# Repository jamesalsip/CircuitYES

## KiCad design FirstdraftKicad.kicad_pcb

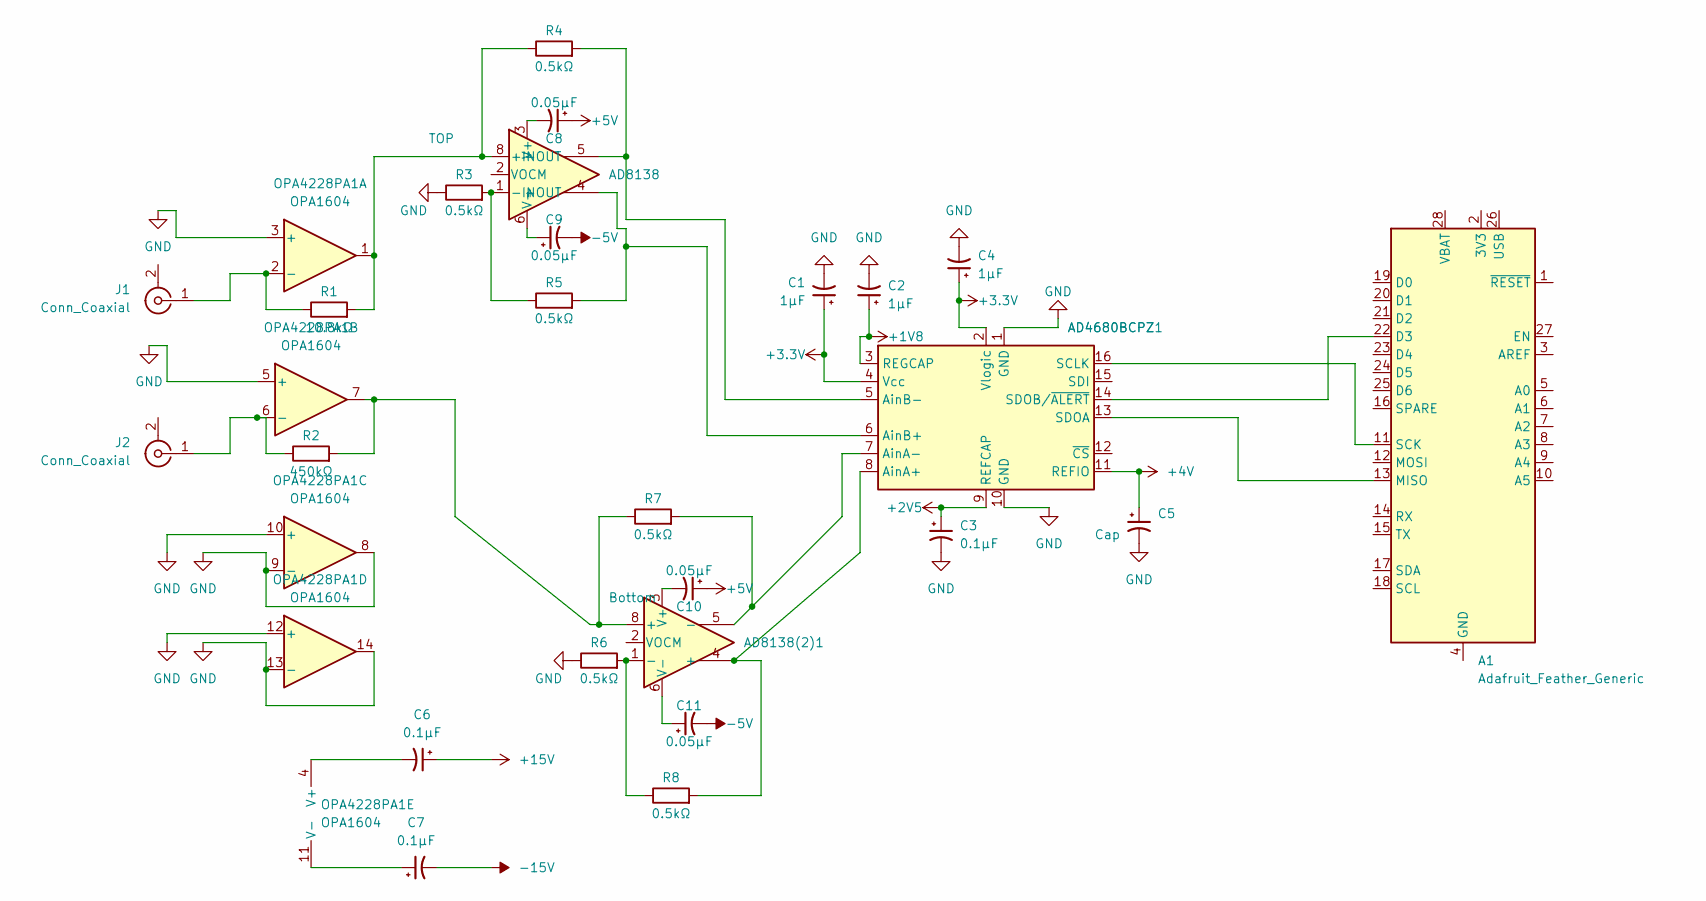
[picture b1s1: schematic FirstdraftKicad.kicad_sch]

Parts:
A1: Adafruit_Feather_Generic; Adafruit_Feather
AD4680BCPZ1: AD4680BCPZ; LGA-16_3x3mm_P0.5mm
AD8138: TOP; DFN-8-1EP_3x3mm_P0.5mm_EP1.66x2.38mm
AD8138(2)1: Bottom; DFN-8-1EP_3x3mm_P0.5mm_EP1.66x2.38mm
C1, C2, C4: 1µF; CP_EIA-1608-10_AVX-L_Pad1.25x1.05mm_HandSolder
C3, C6, C7: 0.1µF; CP_EIA-1608-10_AVX-L_Pad1.25x1.05mm_HandSolder
C5: Cap; CP_EIA-1608-10_AVX-L_Pad1.25x1.05mm_HandSolder
C8, C9, C10, C11: 0.05µF; CP_EIA-1608-10_AVX-L_Pad1.25x1.05mm_HandSolder
J1, J2: Conn_Coaxial; MMCX_Molex_73415-1471_Vertical
OPA4228PA1: OPA1604; DIP-14_W7.62mm
R1: 10.8kΩ; R_0201_0603Metric_Pad0.64x0.40mm_HandSolder
R2: 450kΩ; R_0201_0603Metric_Pad0.64x0.40mm_HandSolder
R3, R4, R5, R6, R7, R8: 0.5kΩ; R_0201_0603Metric_Pad0.64x0.40mm_HandSolder

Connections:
+1V8: AD4680BCPZ1.3 (REGCAP), C2.1
+2V5: AD4680BCPZ1.9 (REFCAP), C3.1
+3V3: AD4680BCPZ1.2 (Vlogic), AD4680BCPZ1.4 (Vcc), C1.1, C4.1
+4V: AD4680BCPZ1.11 (REFIO), C5.1
+5V: C8.1, C10.1
+15V: C6.1
-5V: C9.2, C11.2
-15V: C7.2
GND: AD4680BCPZ1.1 (GND), AD4680BCPZ1.10 (GND), C1.2, C2.2, C3.2, C4.2, C5.2, OPA4228PA1.3 (+), OPA4228PA1.5 (+), OPA4228PA1.8, OPA4228PA1.9 (-), OPA4228PA1.10 (+), OPA4228PA1.12 (+), OPA4228PA1.13 (-), OPA4228PA1.14, R3.1, R6.1
unnamed: AD4680BCPZ1.5 (AinB-), AD8138.5 (-OUT), R4.2
unnamed: AD4680BCPZ1.6 (AinB+), AD8138.4 (+OUT), R5.2
unnamed: AD4680BCPZ1.7 (AinA-), AD8138(2)1.5 (-), R7.2
unnamed: AD4680BCPZ1.8 (AinA+), AD8138(2)1.4 (+), R8.2
unnamed: A1.13 (MISO), AD4680BCPZ1.13 (SDOA)
unnamed: A1.22 (D3), AD4680BCPZ1.14 (SDOB/~ALERT)
unnamed: A1.11 (SCK), AD4680BCPZ1.16 (SCLK)
unnamed: AD8138(2)1.1 (-), R6.2, R8.1
unnamed: AD8138(2)1.3 (V+), C10.2
unnamed: AD8138(2)1.6 (V-), AD8138(2)1.9 (V-), C11.1
unnamed: AD8138(2)1.8 (+), OPA4228PA1.7, R2.2, R7.1
unnamed: AD8138.1 (-IN), R3.2, R5.1
unnamed: AD8138.3 (V+), C8.2
unnamed: AD8138.6 (V-), AD8138.9 (V-), C9.1
unnamed: AD8138.8 (+IN), OPA4228PA1.1, R1.2, R4.1
unnamed: C6.2, OPA4228PA1.4 (V+)
unnamed: C7.1, OPA4228PA1.11 (V-)
unnamed: J1.1 (In), OPA4228PA1.2 (-), R1.1
unnamed: J2.1 (In), OPA4228PA1.6 (-), R2.1

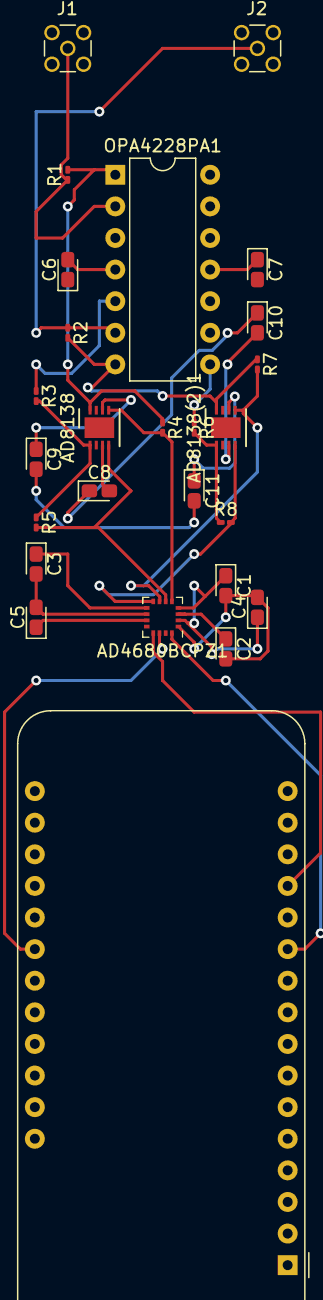
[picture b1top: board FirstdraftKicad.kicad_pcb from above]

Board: 2 copper layers, 26 parts (0 on the bottom side), 26 nets.

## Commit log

2022-07-05 Updated kicad files
